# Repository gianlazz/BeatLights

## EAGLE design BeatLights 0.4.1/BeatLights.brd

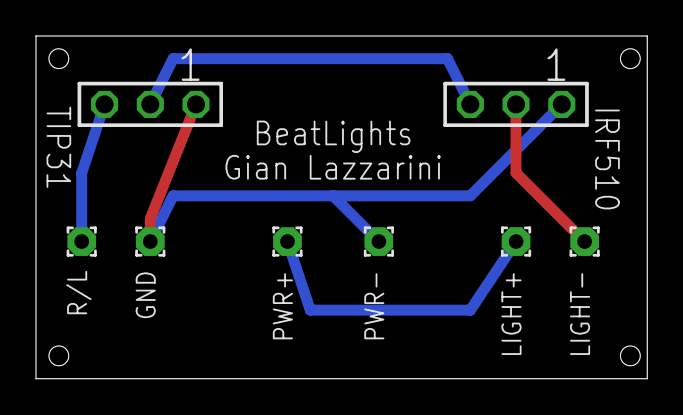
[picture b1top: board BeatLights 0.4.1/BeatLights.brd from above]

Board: 2 copper layers, 34.0 x 19.0 mm, 8 parts (0 on the bottom side), 5 nets.

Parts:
GND: 1,6/0,8
IRF510: SSW-103-02-S-S
LIGHT+: 1,6/0,8
LIGHT-: 1,6/0,8
PWR+: 1,6/0,8
PWR-: 1,6/0,8
R/L: 1,6/0,8
TIP31: Tip31; SSW-103-02-S-S

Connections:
unnamed: R/L.1, TIP31.3
unnamed: IRF510.3, TIP31.2
unnamed: IRF510.2, LIGHT-.1
unnamed: GND.1, IRF510.1, PWR-.1, TIP31.1
unnamed: LIGHT+.1, PWR+.1

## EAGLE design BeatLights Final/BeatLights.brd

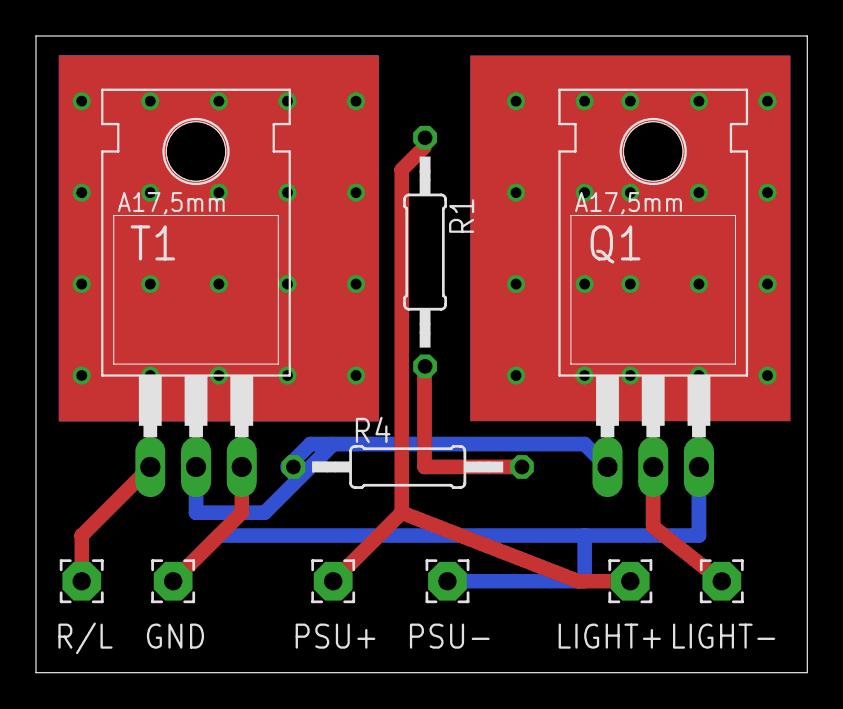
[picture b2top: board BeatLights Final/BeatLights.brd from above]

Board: 2 copper layers, 42.9 x 35.4 mm, 10 parts (0 on the bottom side), 6 nets.

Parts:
GND: 2,15/1,0
LIGHT+: 2,15/1,0
LIGHT-: 2,15/1,0
PSU+: 2,15/1,0
PSU-: 2,15/1,0
Q1: IRF510; TO220
R1, R4: 0207/12
R/L: 2,15/1,0
T1: TIP31; TO220

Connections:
unnamed: R/L.1, T1.1
unnamed: LIGHT-.1, Q1.2
unnamed: R1.2, R4.2
unnamed: GND.1, PSU-.1, Q1.3, T1.3
unnamed: LIGHT+.1, PSU+.1, R1.1
unnamed: Q1.1, R4.1, T1.2

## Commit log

2014-04-29 BeatLights Design Files
    BeatLights 0.4.1 was pre-release
    BeatLights Final was for the kickstarted release
    The eps files are vectors for CNC machining the box
    The .brd are the eagle cad PCB files
2014-05-11 Included Schematics
2016-02-15 git ignore DS_Store
